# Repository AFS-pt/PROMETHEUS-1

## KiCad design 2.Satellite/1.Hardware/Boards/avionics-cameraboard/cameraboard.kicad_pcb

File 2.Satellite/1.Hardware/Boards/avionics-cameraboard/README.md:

avionics-cameraboard
Version B3/02
for updated versions, please consult https://github.com/PyCubed-Mini/avionics-cameraboard

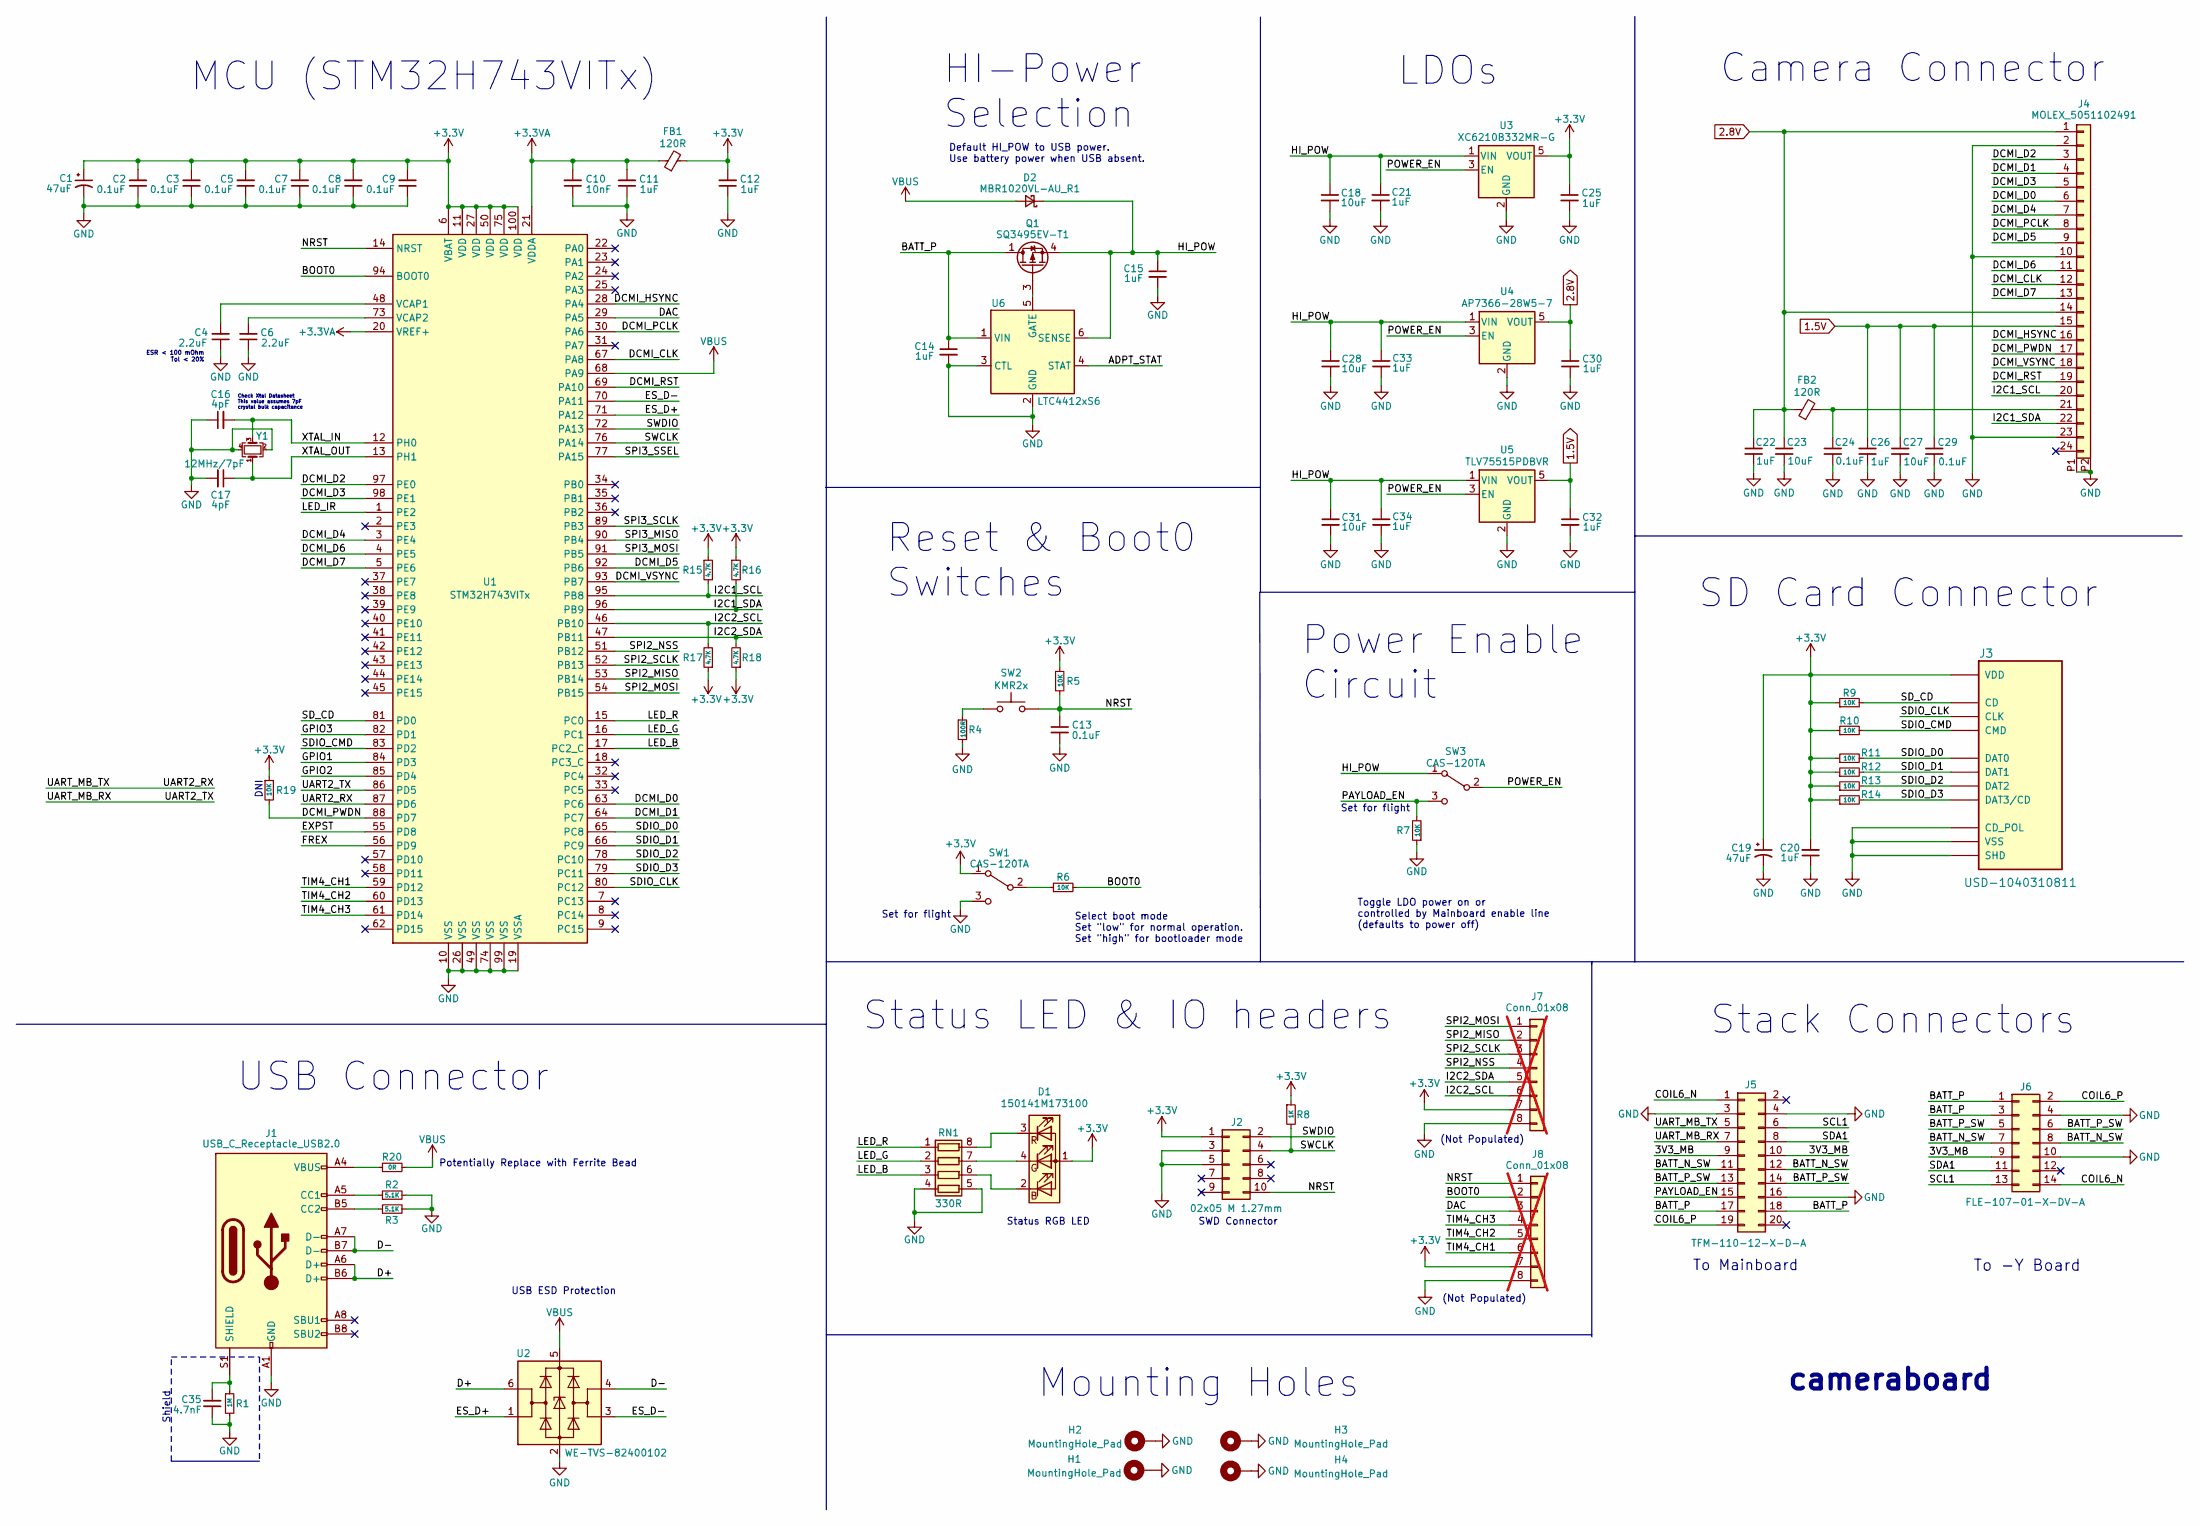
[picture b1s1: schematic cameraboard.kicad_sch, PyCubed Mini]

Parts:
C1, C19: 47uF; CP_EIA-2012-12_Kemet-R
C2, C3, C5, C7, C8, C9, C13, C24, C29: 0.1uF; C_0603_1608Metric
C4, C6: 2.2uF; C_0603_1608Metric
C10: 10nF; C_0603_1608Metric
C11, C12, C14, C15, C20, C21, C22, C25, C26, C30, C32, C33, C34: 1uF; C_0603_1608Metric
C16, C17: 4pF; C_0603_1608Metric
C18, C23, C27, C28, C31: 10uF; C_0603_1608Metric
C35: 4.7nF; C_0603_1608Metric
D1: 150141M173100; LED_RGB_Wuerth-PLCC4_3.2x2.8mm_150141M173100
D2: MBR1020VL-AU_R1; D_SOD-123F
FB1, FB2: 120R; L_0603_1608Metric
H1, H2, H3, H4: MountingHole_Pad; MountingHole
J1: USB_C_Receptacle_USB2.0; USB_C_Receptacle_HRO_TYPE-C-31-M-12
J2: 02x05 M 1.27mm; PinHeader_2x05_P1.27mm_Vertical_SMD
J3: USD-1040310811; microSD_HC_Molex_104031-0811
J4: MOLEX_5051102491
J5: TFM-110-12-X-D-A; SAMTEC_TFM-110-12-X-D-A
J6: FLE-107-01-X-DV-A; SAMTEC_FLE-107-01-X-DV-A
J7, J8: Conn_01x08; PinHeader_1x08_P2.54mm_Vertical; not fitted
Q1: SQ3495EV-T1; SOT-23-6
R1: 1M; R_0603_1608Metric
R2, R3: 5.1K; R_0603_1608Metric
R4: 100R; R_0603_1608Metric
R5, R6, R7, R9, R10, R11, R12, R13, R14, R19: 10K; R_0603_1608Metric
R8: 1K; R_0603_1608Metric
R15, R16, R17, R18: 4.7K; R_0603_1608Metric
R20: 0R; R_0603_1608Metric
RN1: 330R; R_Array_Concave_4x0603
SW1, SW3: CAS-120TA
SW2: KMR2x; BTN_KMR2
U1: STM32H743VITx; LQFP-100_14x14mm_P0.5mm
U2: WE-TVS-82400102; SOT-23-6
U3: XC6210B332MR-G; SOT-23-5
U4: AP7366-28W5-7; SOT-23-5
U5: TLV75515PDBVR; SOT-23-5
U6: LTC4412xS6; TSOT-23-6
Y1: 12MHz/7pF; Crystal_SMD_2520-4Pin_2.5x2.0mm

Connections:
1.5V: C26.1, C27.1, C29.1, C32.1, J4.15, U5.5 (VOUT)
2.8V: C22.1, C23.1, C30.1, FB2.1, J4.1, J4.14, U4.5 (VOUT)
+3.3V: C1.1, C2.2, C3.2, C5.2, C7.2, C8.2, C9.2, C12.2, C19.1, C20.2, C25.1, D1.1 (A), FB1.2, J2.1, J3.4 (VDD), J7.7, J8.7, R5.1, R8.1, R9.1, R10.1, R11.1, R12.1, R13.1, R14.1, R15.1, R16.1, R17.1, R18.1, R19.1, SW1.1 (A), U1.6 (VBAT), U1.11 (VDD), U1.27 (VDD), U1.50 (VDD), U1.75 (VDD), U1.100 (VDD), U3.5 (VOUT)
+3.3VA: C10.2, C11.2, FB1.1, U1.20 (VREF+), U1.21 (VDDA)
/3V3_MB: J5.9, J5.10, J6.9
/ADPT_STAT: U6.4 (STAT)
/BATT_N_SW: J5.11, J5.12, J6.7, J6.8
/BATT_P: C14.1, J5.17, J5.18, J6.1, J6.3, Q1.1 (D), Q1.2 (D), Q1.5 (D), Q1.6 (D), U6.1 (VIN)
/BATT_P_SW: J5.13, J5.14, J6.5, J6.6
/BOOT0: J8.2, R6.2, U1.94 (BOOT0)
/COIL6_N: J5.1, J6.14
/COIL6_P: J5.19, J6.2
/D+: J1.A6 (D+), J1.B6 (D+), U2.6 (I/O1)
/D-: J1.A7 (D-), J1.B7 (D-), U2.4 (I/O2)
/DAC: J8.3, U1.29 (PA5)
/DCMI_CLK: J4.12, U1.67 (PA8)
/DCMI_D0: J4.6, U1.63 (PC6)
/DCMI_D1: J4.4, U1.64 (PC7)
/DCMI_D2: J4.3, U1.97 (PE0)
/DCMI_D3: J4.5, U1.98 (PE1)
/DCMI_D4: J4.7, U1.3 (PE4)
/DCMI_D5: J4.9, U1.92 (PB6)
/DCMI_D6: J4.11, U1.4 (PE5)
/DCMI_D7: J4.13, U1.5 (PE6)
/DCMI_HSYNC: J4.16, U1.28 (PA4)
/DCMI_PCLK: J4.8, U1.30 (PA6)
/DCMI_PWDN: J4.17, R19.2, U1.88 (PD7)
/DCMI_RST: J4.19, U1.69 (PA10)
/DCMI_VSYNC: J4.18, U1.93 (PB7)
/ES_D+: U1.71 (PA12), U2.1 (I/O1)
/ES_D-: U1.70 (PA11), U2.3 (I/O2)
/EXPST: U1.55 (PD8)
/FREX: U1.56 (PD9)
/GPIO1: U1.84 (PD3)
/GPIO2: U1.85 (PD4)
/GPIO3: U1.82 (PD1)
/HI_POW: C15.1, C18.1, C21.1, C28.1, C31.1, C33.1, C34.1, D2.1 (K), Q1.4 (S), SW3.1 (A), U3.1 (VIN), U4.1 (VIN), U5.1 (VIN), U6.6 (SENSE)
/I2C1_SCL: J4.20, R15.2, U1.95 (PB8)
/I2C1_SDA: J4.22, R16.2, U1.96 (PB9)
/I2C2_SCL: J7.6, R17.2, U1.46 (PB10)
/I2C2_SDA: J7.5, R18.2, U1.47 (PB11)
/LED_B: RN1.3 (R3.1), U1.17 (PC2_C)
/LED_G: RN1.2 (R2.1), U1.16 (PC1)
/LED_IR: U1.1 (PE2)
/LED_R: RN1.1 (R1.1), U1.15 (PC0)
/NRST: C13.1, J2.10, J8.1, R5.2, SW2.2, U1.14 (NRST)
/PAYLOAD_EN: J5.15, R7.2, SW3.3 (C)
/POWER_EN: SW3.2 (B), U3.3 (EN), U4.3 (EN), U5.3 (EN)
/SCL1: J5.6, J6.13
/SDA1: J5.8, J6.11
/SDIO_CLK: J3.5 (CLK), U1.80 (PC12)
/SDIO_CMD: J3.3 (CMD), R10.2, U1.83 (PD2)
/SDIO_D0: J3.7 (DAT0), R11.2, U1.65 (PC8)
/SDIO_D1: J3.8 (DAT1), R12.2, U1.66 (PC9)
/SDIO_D2: J3.1 (DAT2), R13.2, U1.78 (PC10)
/SDIO_D3: J3.2 (DAT3/CD), R14.2, U1.79 (PC11)
/SD_CD: J3.10 (CD), R9.2, U1.81 (PD0)
/SPI2_MISO: J7.2, U1.53 (PB14)
/SPI2_MOSI: J7.1, U1.54 (PB15)
/SPI2_NSS: J7.4, U1.51 (PB12)
/SPI2_SCLK: J7.3, U1.52 (PB13)
/SPI3_MISO: U1.90 (PB4)
/SPI3_MOSI: U1.91 (PB5)
/SPI3_SCLK: U1.89 (PB3)
/SPI3_SSEL: U1.77 (PA15)
/SWCLK: J2.4, R8.2, U1.76 (PA14)
/SWDIO: J2.2, U1.72 (PA13)
/TIM4_CH1: J8.6, U1.59 (PD12)
/TIM4_CH2: J8.5, U1.60 (PD13)
/TIM4_CH3: J8.4, U1.61 (PD14)
/UART2_RX: J5.5, U1.87 (PD6)
/UART2_TX: J5.7, U1.86 (PD5)
/XTAL_IN: C16.2, U1.12 (PH0), Y1.3
/XTAL_OUT: C17.1, U1.13 (PH1), Y1.1
GND: C1.2, C2.1, C3.1, C4.1, C5.1, C6.1, C7.1, C8.1, C9.1, C10.1, C11.1, C12.1, C13.2, C14.2, C15.2, C16.1, C17.2, C18.2, C19.2, C20.1, C21.2, C22.2, C23.2, C24.2, C25.2, C26.2, C27.2, C28.2, C29.2, C30.2, C31.2, C32.2, C33.2, C34.2, C35.1, H1.1, H2.1, H3.1, H4.1, J1.A1 (GND), J1.A12 (GND), J1.B1 (GND), J1.B12 (GND), J2.3, J2.5, J3.6 (VSS), J3.9 (CD_POL), J3.11 (SHD), J4.2, J4.10, J4.23, J4.P1, J4.P2, J5.3, J5.4, J5.16, J6.4, J6.10, J7.8, J8.8, R1.2, R2.2, R3.2, R4.2, R7.1, RN1.4 (R4.1), RN1.5 (R4.2), SW1.3 (C), U1.10 (VSS), U1.19 (VSSA), U1.26 (VSS), U1.49 (VSS), U1.74 (VSS), U1.99 (VSS), U2.2 (GND), U3.2 (GND), U4.2 (GND), U5.2 (GND), U6.2 (GND), U6.3 (CTL), Y1.2, Y1.4
unnamed: D1.2 (BK), RN1.6 (R3.2)
unnamed: D1.4 (GK), RN1.7 (R2.2)
unnamed: D1.3 (RK), RN1.8 (R1.2)
unnamed: J1.A5 (CC1), R2.1
unnamed: J1.B5 (CC2), R3.1
unnamed: C35.2, J1.S1 (SHIELD), R1.1
unnamed: J1.A4 (VBUS), J1.A9 (VBUS), J1.B4 (VBUS), J1.B9 (VBUS), R20.1
unnamed: C24.1, FB2.2, J4.21
unnamed: Q1.3 (G), U6.5 (GATE)
unnamed: R4.1, SW2.1
unnamed: R6.1, SW1.2 (B)
unnamed: C4.2, U1.48 (VCAP1)
unnamed: C6.2, U1.73 (VCAP2)
VBUS: D2.2 (A), R20.2, U1.68 (PA9), U2.5 (VBUS)

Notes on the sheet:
Mounting Holes
Set for flight
cameraboard
SD Card Connector
(Not Populated)
Check Xtal Datasheet This value assumes 7pF crystal bulk capacitance
Power Enable Circuit
HI-Power Selection
To Mainboard
To -Y Board
Potentially Replace with Ferrite Bead
Status LED & IO headers
DNI
MCU (STM32H743VITx)
Status RGB LED
SWD Connector
Reset & Boot0 Switches
Stack Connectors
Toggle LDO power on or controlled by Mainboard enable line (defaults to power off)
Shield
LDOs
Select boot mode Set "low" for normal operation. Set "high" for bootloader mode
USB Connector
Camera Connector
ESR < 100 mOhm Tol < 20%
Default HI_POW to USB power. Use battery power when USB absent.
USB ESD Protection

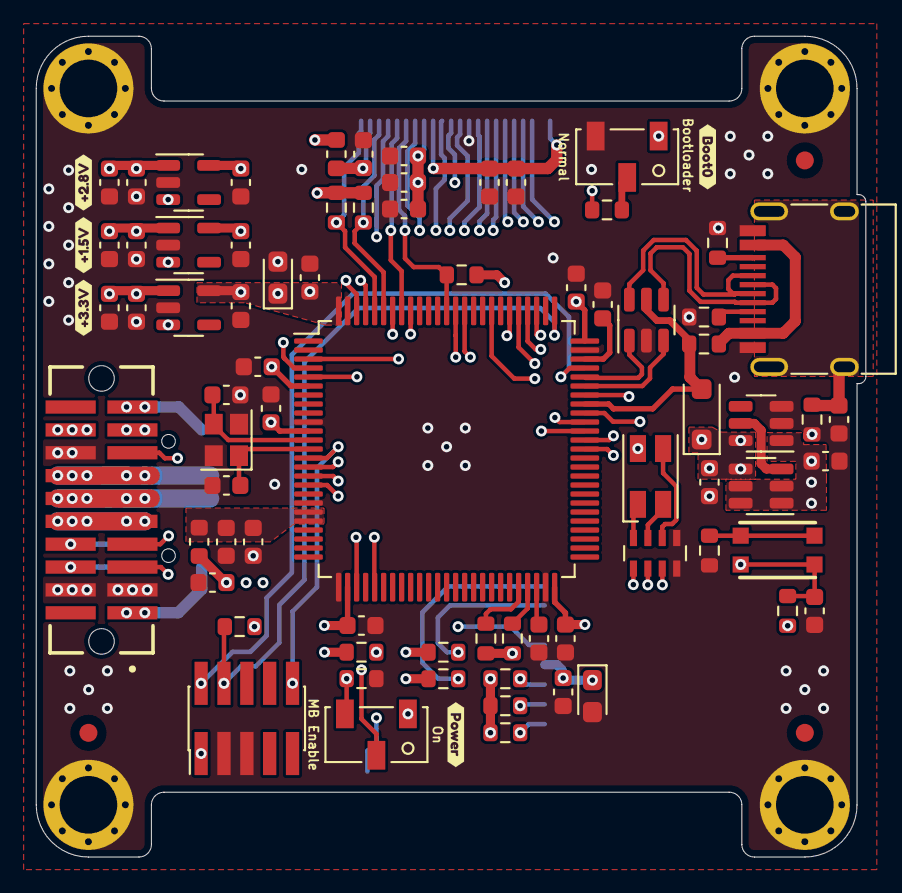
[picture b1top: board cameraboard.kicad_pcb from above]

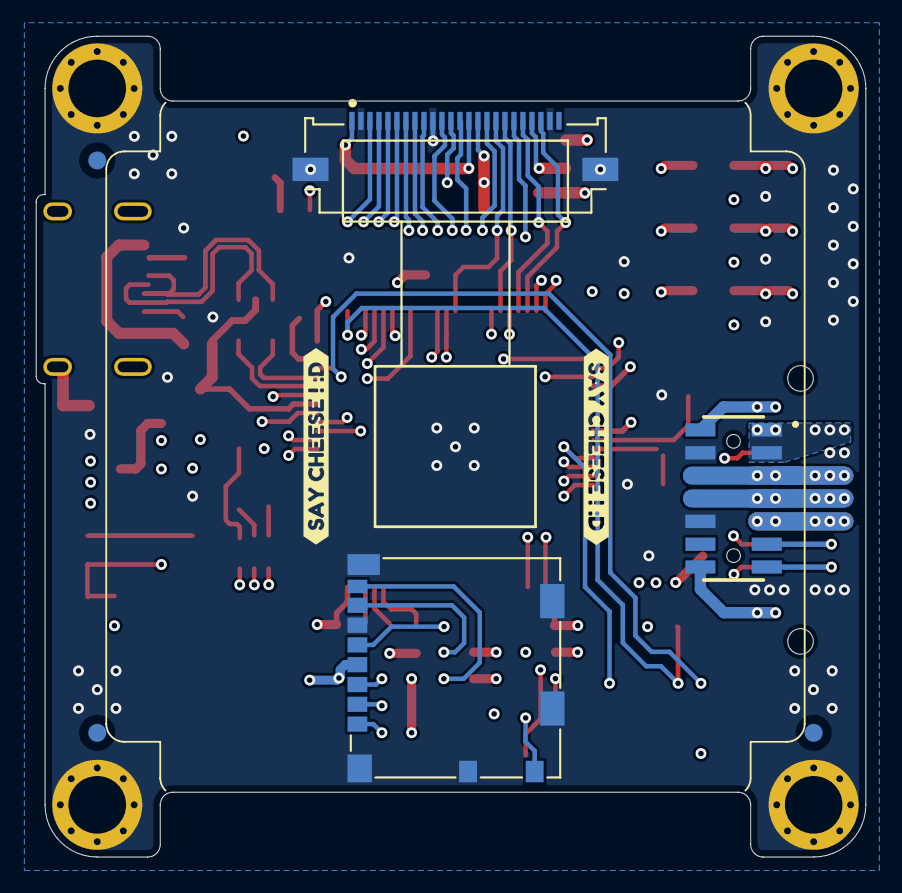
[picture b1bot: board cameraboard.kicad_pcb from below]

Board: 4 copper layers, 46.1 x 45.6 mm, 89 parts (5 on the bottom side), 70 nets.

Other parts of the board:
Ref**: Val**; pycubed_mini_half
kibuzzard-63E3EA3E: G***; kibuzzard-63E3EA3E
kibuzzard-63E3EAF3: G***; kibuzzard-63E3EAF3
kibuzzard-63E3EBF1: G***; kibuzzard-63E3EBF1
kibuzzard-63E3EC1C: G***; kibuzzard-63E3EC1C
kibuzzard-63E3EC09: G***; kibuzzard-63E3EC09
kibuzzard-63E3ED57, kibuzzard-63E3ED57#2: G***; kibuzzard-63E3ED57

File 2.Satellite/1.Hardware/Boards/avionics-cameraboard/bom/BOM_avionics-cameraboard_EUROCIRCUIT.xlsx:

Board | Reference Designator | Value | Quantity | GenericPart(EuroCircuit) | Manufacturer Part Number | URL
avionics-cameraboard | C1, C19 | 47uF | 2 |  | F981A476MSA
avionics-cameraboard | C10 | 10nF | 1 | GPC0603103 | 06031C103K4T4A
avionics-cameraboard | C11, C12, C14, C15, C20, C21, C22, C25, C26, C30, C32, C33, C34 | 1uF | 13 | GPC0603105 | GRT188R61H105KE13D
avionics-cameraboard | C16, C17 | 4pF | 2 |  | CGA3E2C0G1H040C080AA
avionics-cameraboard | C18, C23, C27, C28, C31 | 10uF | 5 |  | GRT188R61C106KE13D
avionics-cameraboard | C2, C3, C5, C7, C8, C9, C13, C24, C29 | 0.1uF | 9 | GPC0603104 | 06035C104K4T2A
avionics-cameraboard | C35 | 4.7nF | 1 | GPC0603472 | 06031C472K4T4A
avionics-cameraboard | C4, C6 | 2.2uF | 2 |  | GRT188R61H225KE13D
avionics-cameraboard | D1 | 150141M173100 | 1 |  | 150141M173100 | https://www.digikey.pt/pt/products/detail/würth-elektronik/1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
avionics-cameraboard | D2 | MBR1020VL-AU_R1 | 1 |  | MBR1020VL-AU_R1_000A1 | https://www.digikey.pt/pt/products/detail/panjit-internation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
avionics-cameraboard | FB1, FB2 | 120R | 2 |  | BLM18AG121SH1D | https://www.digikey.pt/pt/products/detail/murata-electronics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
avionics-cameraboard | J1 | USB_C_Receptacle_USB2.0 | 1 |  | USB4105-GF-A | https://www.digikey.pt/pt/products/detail/gct/USB4105-GF-A/11198441
avionics-cameraboard | J2 | 02x05 M 1.27mm | 1 |  | 20021121-00010C4LF | https://www.digikey.pt/pt/products/detail/amphenol-cs-fci/20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
avionics-cameraboard | J3 | USD-1040310811 | 1 |  | 1040310811 | https://www.digikey.pt/pt/products/detail/molex/1040310811/2370379
avionics-cameraboard | J4 | MOLEX_5051102491 | 1 |  | 5051102491 | https://www.digikey.pt/pt/products/detail/molex/5051102491/5254657
avionics-cameraboard | J5 | TFM-110-12-X-D-A | 1 |  | TFM-110-12-L-D-A | https://www.digikey.pt/pt/products/detail/samtec-inc/TFM-110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
avionics-cameraboard | J6 | FLE-107-01-X-DV-A | 1 |  | FLE-107-01-G-DV-A | https://www.digikey.pt/pt/products/detail/samtec-inc/FLE-107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
avionics-cameraboard | Q1 | SQ3495EV-T1 | 1 |  | SQ3495EV-T1_GE3 | https://www.digikey.pt/pt/products/detail/vishay-siliconix/S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
avionics-cameraboard | R1 | 1M | 1 |  | RNCF0603BKC1M00
avionics-cameraboard | R15, R16, R17, R18 | 4.7K | 4 | GPR06034K7 | RNCF0603DTE4K70
avionics-cameraboard | R2, R3 | 5.1K | 2 | GPR06035K1 | RNCF0603DTE5K10
avionics-cameraboard | R20 | 0R | 1 |  | RMCF0603ZT0R00
avionics-cameraboard | R4 | 100R | 1 | GPR0603100R | RNCF0603DTE100R
avionics-cameraboard | R5, R6, R7, R9, R10, R11, R12, R13, R14, R19 | 10K | 10 |  | RNCF0603BTE10K0
avionics-cameraboard | R8 | 1K | 1 |  | RNCF0603DTE1K00
avionics-cameraboard | RN1 | 330R | 1
avionics-cameraboard | SW1, SW3 | CAS-120TA | 2 |  | CAS-120TA | https://www.digikey.pt/pt/products/detail/nidec-components-c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
avionics-cameraboard | SW2 | KMR2x | 1 |  | KMR241NG ULC LFS | https://www.digikey.pt/pt/products/detail/c-k/KMR241NG-ULC-L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
avionics-cameraboard | U1 | STM32H743VITx | 1 |  | STM32H743VIT6 | https://www.digikey.pt/pt/products/detail/stmicroelectronics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
avionics-cameraboard | U2 | WE-TVS-82400102 | 1 |  | 82400102 | https://www.digikey.pt/pt/products/detail/würth-elektronik/8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
avionics-cameraboard | U3 | XC6210B332MR-G | 1 |  | XC6210B332MR-G | https://www.digikey.pt/pt/products/detail/torex-semiconducto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
avionics-cameraboard | U4 | AP7366-28W5-7 | 1 |  | AP7366-28W5-7 | https://www.digikey.pt/pt/products/detail/diodes-incorporate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
avionics-cameraboard | U5 | TLV75515PDBVR | 1 |  | TLV75515PDBVR | https://www.digikey.pt/pt/products/detail/texas-instruments/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
avionics-cameraboard | U6 | LTC4412xS6 | 1 |  | LTC4412ES6#TRMPBF | https://www.digikey.pt/pt/products/detail/analog-devices-inc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
avionics-cameraboard | Y1 | 12MHz/7pF | 1 |  | ECS-160-10-36Q-ES-TR | https://www.digikey.pt/pt/products/detail/ecs-inc/ECS-160-10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

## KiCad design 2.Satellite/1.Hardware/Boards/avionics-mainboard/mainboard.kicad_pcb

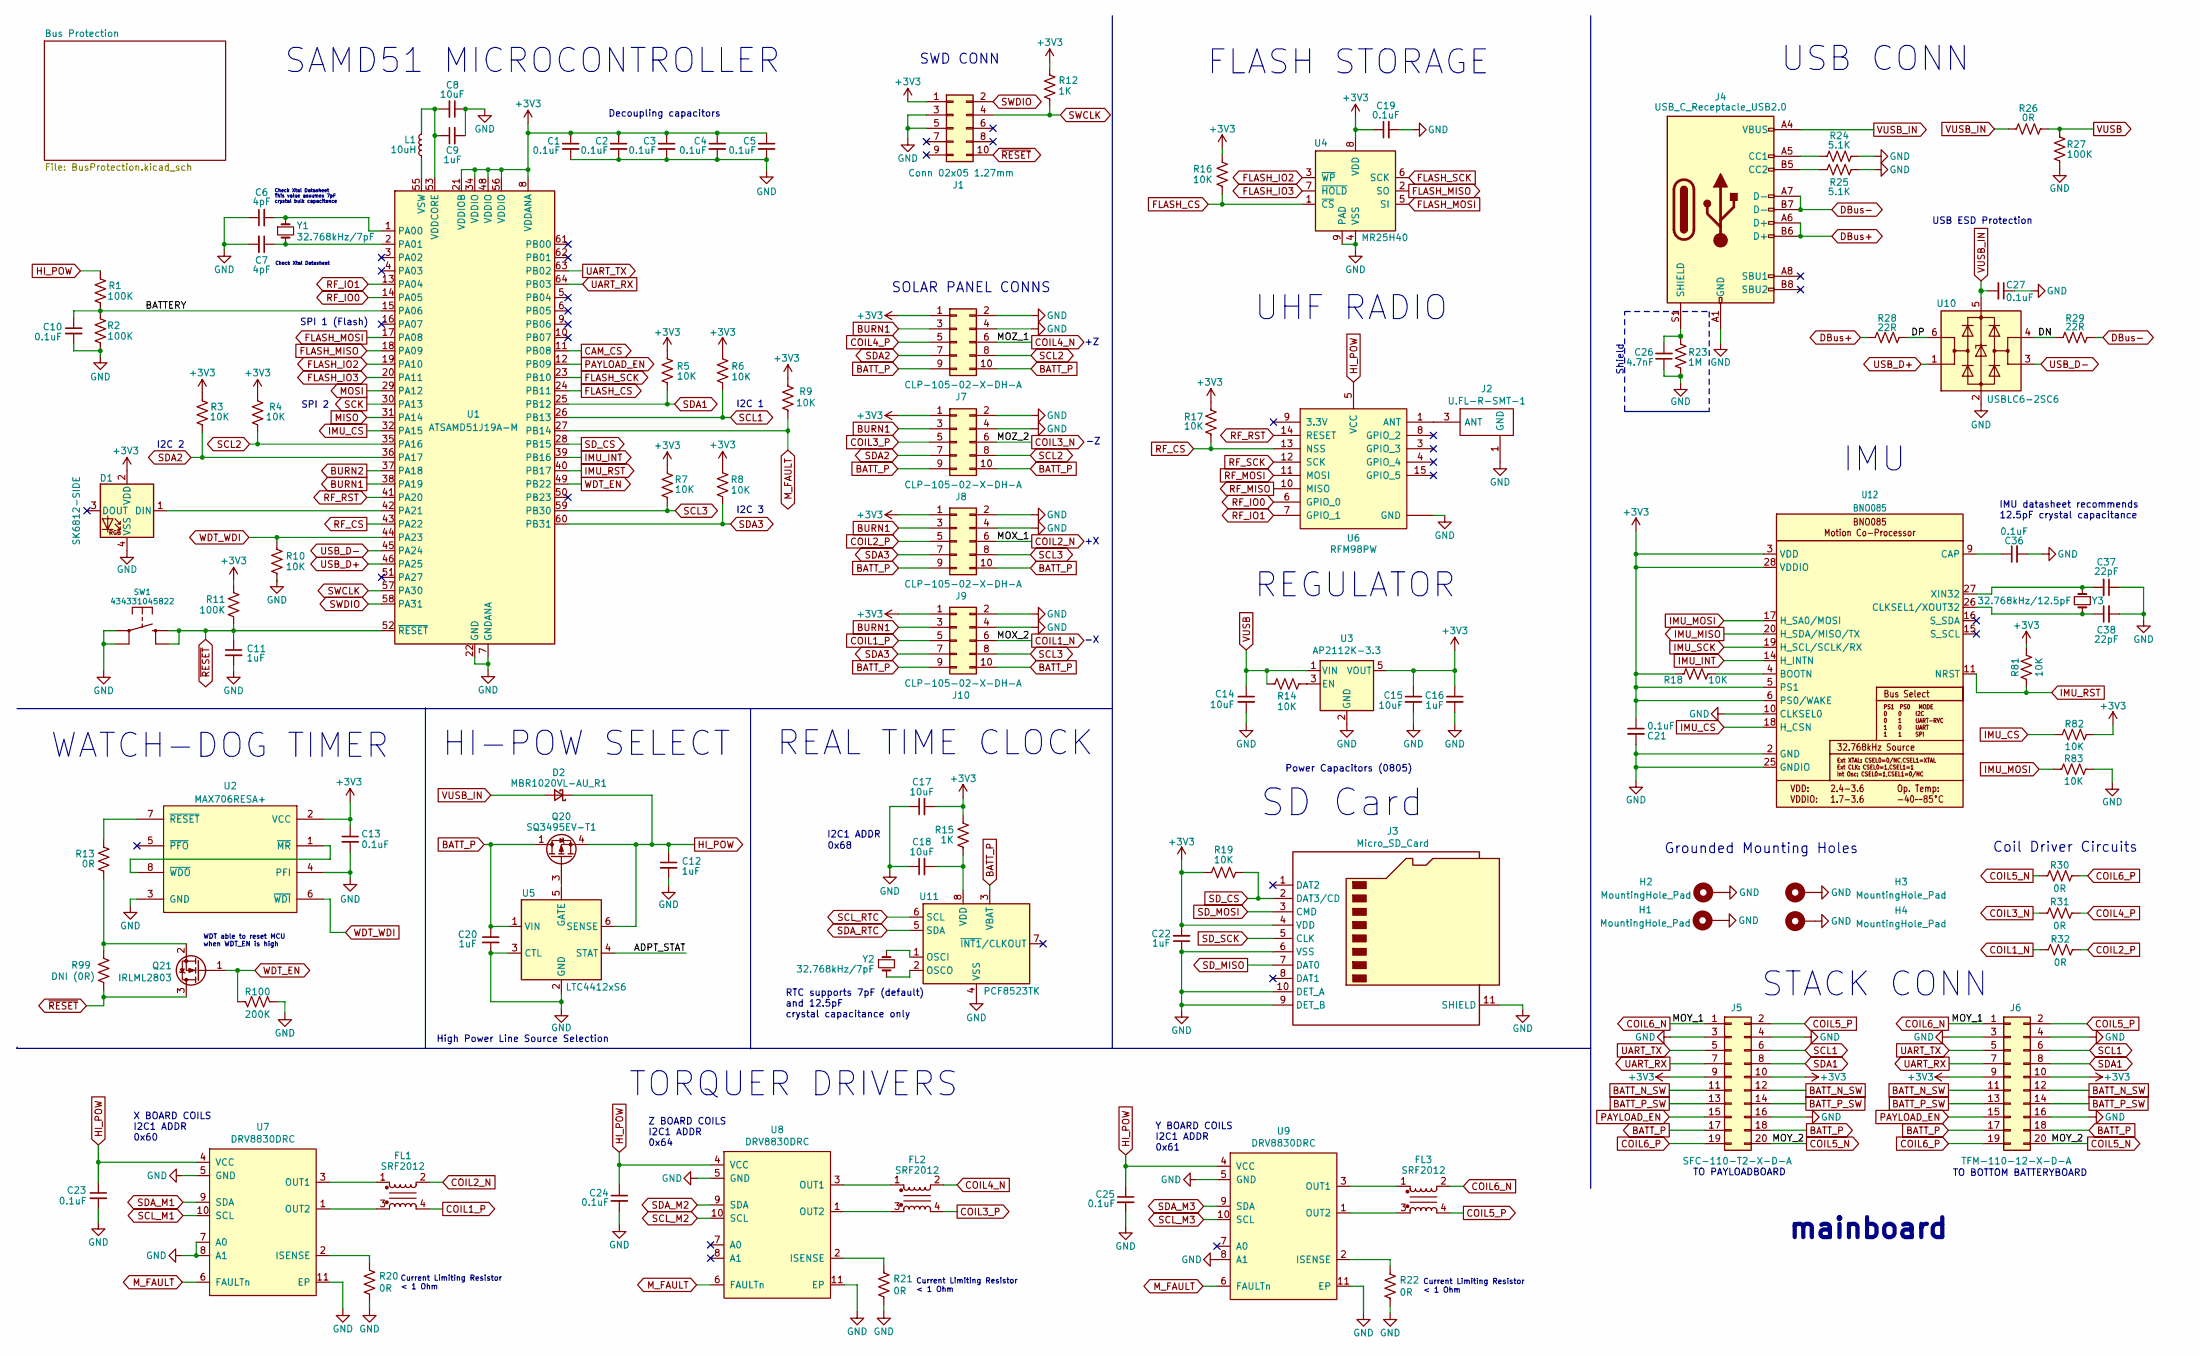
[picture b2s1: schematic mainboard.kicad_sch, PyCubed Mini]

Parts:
C1, C2, C3, C4, C5, C10, C13, C19, C21, C23, C24, C25, C27, C36: 0.1uF; C_0603_1608Metric
C6, C7: 4pF; C_0603_1608Metric
C8, C17, C18: 10uF; C_0603_1608Metric
C9, C11, C12, C20, C22: 1uF; C_0603_1608Metric
C14, C15: 10uF; C_0805_2012Metric
C16: 1uF; C_0805_2012Metric
C26: 4.7nF; C_0603_1608Metric
C37, C38: 22pF; C_0603_1608Metric
D1: SK6812-SIDE
D2: MBR1020VL-AU_R1; D_SOD-123F
FL1, FL2, FL3: SRF2012
H1, H2, H3, H4: MountingHole_Pad; MountingHole
J1: Conn 02x05 1.27mm; PinHeader_2x05_P1.27mm_Vertical_SMD
J2: U.FL-R-SMT-1; Manufacturer_Part_Number U.FL-R-SMT-1
J3: Micro_SD_Card; microSD_104031-0811
J4: USB_C_Receptacle_USB2.0; USB_C_Receptacle_HRO_TYPE-C-31-M-12
J5: SFC-110-T2-X-D-A; SAMTEC_SFC-110-T2-X-D-A
J6: TFM-110-12-X-D-A; SAMTEC_TFM-110-12-X-D-A
J7, J8, J9, J10: CLP-105-02-X-DH-A; SAMTEC_CLP-105-02-X-DH-A
L1: 10uH; L_0805_2012Metric
Q20: SQ3495EV-T1; SOT-23-6
Q21: IRLML2803; SOT-23
R1, R2, R11, R27: 100K; R_0603_1608Metric
R3, R4, R5, R6, R7, R8, R9, R10, R14, R16, R17, R18, R19, R81, R82, R83: 10K; R_0603_1608Metric
R12, R15: 1K; R_0603_1608Metric
R13, R20, R21, R22, R26, R30, R31, R32: 0R; R_0603_1608Metric
R23: 1M; R_0603_1608Metric
R24, R25: 5.1K; R_0603_1608Metric
R28, R29: 22R; R_0603_1608Metric
R99: DNI (0R); R_0603_1608Metric
R100: 200K; R_0603_1608Metric
SW1: 434331045822; SMT_1045822_WRE
U1: ATSAMD51J19A-M; QFN-64-1EP_9x9mm_P0.5mm_EP4.7x4.7mm
U2: MAX706RESA+; SOIC-8_3.9x4.9mm_P1.27mm
U3: AP2112K-3.3; SOT-23-5
U4: MR25H40; MR25H40DF
U5: LTC4412xS6; TSOT-23-6
U6: RFM98PW
U7, U8, U9: DRV8830DRC; VSON-10
U10: USBLC6-2SC6; SOT-23-6
U11: PCF8523TK; HVSON-8-1EP_4x4mm_P0.8mm_EP2.2x3.1mm
U12: BNO085
Y1, Y2: 32.768kHz/7pF; Crystal_SMD_MicroCrystal_CC7V-T1A-2Pin_3.2x1.5mm
Y3: 32.768kHz/12.5pF; Crystal_SMD_MicroCrystal_CC7V-T1A-2Pin_3.2x1.5mm

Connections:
+3V3: C1.1, C2.1, C3.1, C4.1, C5.1, C13.1, C15.1, C16.1, C17.2, C19.1, C21.1, C22.2, D1.2 (VDD), J1.1, J3.4 (VDD), J5.9, J5.10, J6.9, J6.10, J7.1, J8.1, J9.1, J10.1, R3.2, R4.2, R5.2, R6.2, R7.2, R8.2, R9.1, R11.2, R12.2, R15.2, R16.1, R17.2, R18.2, R19.1, R81.2, R82.1, U1.8 (VDDANA), U1.21 (VDDIOB), U1.34 (VDDIO), U1.48 (VDDIO), U1.56 (VDDIO), U2.2 (VCC), U3.5 (VOUT), U4.8 (VDD), U12.3 (VDD), U12.5 (PS1), U12.6 (PS0/WAKE), U12.28 (VDDIO); also elsewhere on the board
/ADPT_STAT: U5.4 (STAT)
/BATTERY: C10.1, R1.1, R2.2, U1.15 (PA06)
/DN: R29.2, U10.4 (I/O2)
/DP: R28.1, U10.6 (I/O1)
BATT_N_SW: J5.11, J5.12, J6.11, J6.12
BATT_P: C20.1, J5.17, J5.18, J6.17, J6.18, J7.9, J7.10, J8.9, J8.10, J9.9, J9.10, J10.9, J10.10, Q20.1 (D), Q20.2 (D), Q20.5 (D), Q20.6 (D), U5.1 (VIN), U11.3 (VBAT)
BATT_P_SW: J5.13, J5.14, J6.13, J6.14
BURN1: J7.3, J8.3, J9.3, J10.3, U1.38 (PA19)
BURN2: U1.37 (PA18)
CAM_CS: U1.11 (PB08)
COIL1_N: J10.6, R32.1
COIL1_P: FL1.4, J10.5
COIL2_N: FL1.2, J9.6
COIL2_P: J9.5, R32.2
COIL3_N: J8.6, R31.1
COIL3_P: FL2.4, J8.5
COIL4_N: FL2.2, J7.6
COIL4_P: J7.5, R31.2
COIL5_N: J5.20, J6.20, R30.2
COIL5_P: FL3.4, J5.2, J6.2
COIL6_N: FL3.2, J5.1, J6.1
COIL6_P: J5.19, J6.19, R30.1
DBus+: J4.A6 (D+), J4.B6 (D+), R28.2
DBus-: J4.A7 (D-), J4.B7 (D-), R29.1
FLASH_CS: R16.2, U1.24 (PB11), U4.1 (~CS)
FLASH_IO2: U1.19 (PA10), U4.3 (~WP)
FLASH_IO3: U1.20 (PA11), U4.7 (~HOLD)
FLASH_MISO: U1.18 (PA09), U4.2 (SO)
FLASH_MOSI: U1.17 (PA08), U4.5 (SI)
FLASH_SCK: U1.23 (PB10), U4.6 (SCK)
GND: C1.2, C2.2, C3.2, C4.2, C5.2, C6.1, C7.2, C8.1, C9.2, C10.2, C11.2, C12.2, C13.2, C14.2, C15.2, C16.2, C17.1, C18.1, C19.2, C20.2, C21.2, C22.1, C23.2, C24.2, C25.2, C26.1, C27.1, C36.2, C37.1, C38.2, D1.4 (VSS), H1.1, H2.1, H3.1, H4.1, J1.3, J1.5, J2.1 (GND), J2.2, J3.6 (VSS), J3.9 (DET_B), J3.10 (DET_A), J3.11 (SHIELD), J4.A1 (GND), J4.A12 (GND), J4.B1 (GND), J4.B12 (GND), J5.3, J5.4, J5.16, J6.3, J6.4, J6.16, J7.2, J7.4, J8.2, J8.4, J9.2, J9.4, J10.2, J10.4, R2.1, R10.1, R20.1, R21.1, R22.1, R23.1, R24.2, R25.2, R27.2, R83.1, R100.2, SW1.1, SW1.3 (P1), U1.7 (GNDANA), U1.22 (GND), U1.33 (GND), U1.47 (GND), U1.54 (GND), U1.65 (GND), U2.3 (GND), U2.4 (PFI), U3.2 (GND), U4.4 (VSS), U4.9 (PAD), U5.2 (GND), U5.3 (CTL), U6.2 (GND), U6.16 (GND), U6.17 (GND), U7.5 (GND), U7.7 (A0), U7.8 (A1), U7.11 (EP), U8.5 (GND), U8.11 (EP), U9.5 (GND), U9.8 (A1), U9.11 (EP), U10.2 (GND), U11.4 (VSS), U11.9 (VSS), U12.2 (GND), U12.10 (CLKSEL0), U12.25 (GNDIO); also elsewhere on the board
HI_POW: C12.1, C23.1, C24.1, C25.1, D2.1 (K), Q20.4 (S), R1.2, U5.6 (SENSE), U6.5 (VCC), U7.4 (VCC), U8.4 (VCC), U9.4 (VCC)
IMU_CS: R82.2, U1.32 (PA15), U12.18 (H_CSN); also elsewhere on the board
IMU_INT: U1.39 (PB16), U12.14 (H_INTN)
IMU_MISO: U12.20 (H_SDA/MISO/TX); also elsewhere on the board
IMU_MOSI: R83.2, U12.17 (H_SA0/MOSI); also elsewhere on the board
IMU_RST: R81.1, U1.40 (PB17), U12.11 (NRST)
IMU_SCK: U12.19 (H_SCL/SCLK/RX); also elsewhere on the board
MISO: U1.31 (PA14); also elsewhere on the board
MOSI: U1.29 (PA12); also elsewhere on the board
M_FAULT: R9.2, U1.27 (PB14), U7.6 (FAULTn), U8.6 (FAULTn), U9.6 (FAULTn)
unnamed: D1.1 (DIN), U1.42 (PA21)
unnamed: J2.3 (ANT), U6.1 (ANT)
unnamed: J4.A5 (CC1), R24.1
unnamed: J4.B5 (CC2), R25.1
unnamed: C26.2, J4.S1 (SHIELD), R23.2
unnamed: Q20.3 (G), U5.5 (GATE)
unnamed: Q21.2 (S), R13.1, R99.2
unnamed: C6.2, U1.1 (PA00), Y1.1
unnamed: C7.1, U1.2 (PA01), Y1.2
unnamed: C8.2, C9.1, L1.1, U1.53 (VDDCORE)
unnamed: L1.2, U1.55 (VSW)
unnamed: U2.1 (~MR), U2.8 (~WDO)
unnamed: R13.2, U2.7 (~RESET)
unnamed: R14.2, U3.3 (EN)
unnamed: R20.2, U7.2 (ISENSE)
unnamed: FL1.1, U7.3 (OUT1)
unnamed: FL1.3, U7.1 (OUT2)
unnamed: R21.2, U8.2 (ISENSE)
unnamed: FL2.1, U8.3 (OUT1)
unnamed: FL2.3, U8.1 (OUT2)
unnamed: R22.2, U9.2 (ISENSE)
unnamed: FL3.1, U9.3 (OUT1)
unnamed: FL3.3, U9.1 (OUT2)
unnamed: U11.1 (OSCI), Y2.1
unnamed: U11.2 (OSCO), Y2.2
unnamed: C18.2, R15.1, U11.8 (VDD)
unnamed: R18.1, U12.4 (BOOTN)
unnamed: C36.1, U12.9 (CAP)
unnamed: C38.1, U12.26 (CLKSEL1/XOUT32), Y3.2
unnamed: C37.2, U12.27 (XIN32), Y3.1
PAYLOAD_EN: J5.15, J6.15, U1.12 (PB09)
RF_CS: R17.1, U1.43 (PA22), U6.13 (NSS); also elsewhere on the board
RF_IO0: U1.14 (PA05), U6.6 (GPIO_0)
RF_IO1: U1.13 (PA04), U6.7 (GPIO_1)
RF_MISO: U6.10 (MISO); also elsewhere on the board
RF_MOSI: U6.11 (MOSI); also elsewhere on the board
RF_RST: U1.41 (PA20), U6.14 (RESET)
RF_SCK: U6.12 (SCK); also elsewhere on the board
SCK: U1.30 (PA13); also elsewhere on the board
SCL1: J5.6, J6.6, R6.1, U1.26 (PB13); also elsewhere on the board
SCL2: J7.8, J8.8, R4.1, U1.35 (PA16)
SCL3: J9.8, J10.8, R7.1, U1.59 (PB30)
SCL_M1: U7.10 (SCL); also elsewhere on the board
SCL_M2: U8.10 (SCL); also elsewhere on the board
SCL_M3: U9.10 (SCL); also elsewhere on the board
SCL_RTC: U11.6 (SCL); also elsewhere on the board
SDA1: J5.8, J6.8, R5.1, U1.25 (PB12); also elsewhere on the board
SDA2: J7.7, J8.7, R3.1, U1.36 (PA17)
SDA3: J9.7, J10.7, R8.1, U1.60 (PB31)
SDA_M1: U7.9 (SDA); also elsewhere on the board
SDA_M2: U8.9 (SDA); also elsewhere on the board
SDA_M3: U9.9 (SDA); also elsewhere on the board
SDA_RTC: U11.5 (SDA); also elsewhere on the board
SD_CS: J3.2 (DAT3/CD), R19.2, U1.28 (PB15); also elsewhere on the board
SD_MISO: J3.7 (DAT0); also elsewhere on the board
SD_MOSI: J3.3 (CMD); also elsewhere on the board
SD_SCK: J3.5 (CLK); also elsewhere on the board
SWCLK: J1.4, R12.1, U1.57 (PA30)
SWDIO: J1.2, U1.58 (PA31)
UART_RX: J5.7, J6.7, U1.64 (PB03)
UART_TX: J5.5, J6.5, U1.63 (PB02)
USB_D+: U1.46 (PA25), U10.1 (I/O1)
USB_D-: U1.45 (PA24), U10.3 (I/O2)
VUSB: C14.1, R14.1, R26.2, R27.1, U3.1 (VIN)
VUSB_IN: C27.2, D2.2 (A), J4.A4 (VBUS), J4.A9 (VBUS), J4.B4 (VBUS), J4.B9 (VBUS), R26.1, U10.5 (VBUS)
WDT_EN: Q21.1 (G), R100.1, U1.49 (PB22)
WDT_WDI: R10.2, U1.44 (PA23), U2.6 (~WDI)
~RESET: C11.1, J1.10, Q21.3 (D), R11.1, R99.1, SW1.2 (S), SW1.4 (S1), U1.52 (~RESET)

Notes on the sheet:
High Power Line Source Selection
X BOARD COILS I2C1 ADDR 0x60
WDT able to reset MCU when WDT_EN is high
Current Limiting Resistor < 1 Ohm
mainboard
0x68
SAMD51 MICROCONTROLLER
FLASH STORAGE
USB ESD Protection
REGULATOR
SOLAR PANEL CONNS
SPI 2
I2C 3
Check Xtal Datasheet
IMU datasheet recommends 12.5pF crystal capacitance
TO BOTTOM BATTERYBOARD
TORQUER DRIVERS
WATCH-DOG TIMER
SWD CONN
Coil Driver Circuits
STACK CONN
Shield
Decoupling capacitors
I2C 2
Z BOARD COILS I2C1 ADDR 0x64
IMU
UHF RADIO
Check Xtal Datasheet This value assumes 7pF crystal bulk capacitance
I2C 1
Grounded Mounting Holes
USB CONN
SD Card
HI-POW SELECT
REAL TIME CLOCK
Y BOARD COILS I2C1 ADDR 0x61
Power Capacitors (0805)
SPI 1 (Flash)
TO PAYLOADBOARD
I2C1 ADDR
RTC supports 7pF (default) and 12.5pF crystal capacitance only

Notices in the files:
parts and their libraries:
Copyright 2021 Accelerated Designs. All rights reserved.
